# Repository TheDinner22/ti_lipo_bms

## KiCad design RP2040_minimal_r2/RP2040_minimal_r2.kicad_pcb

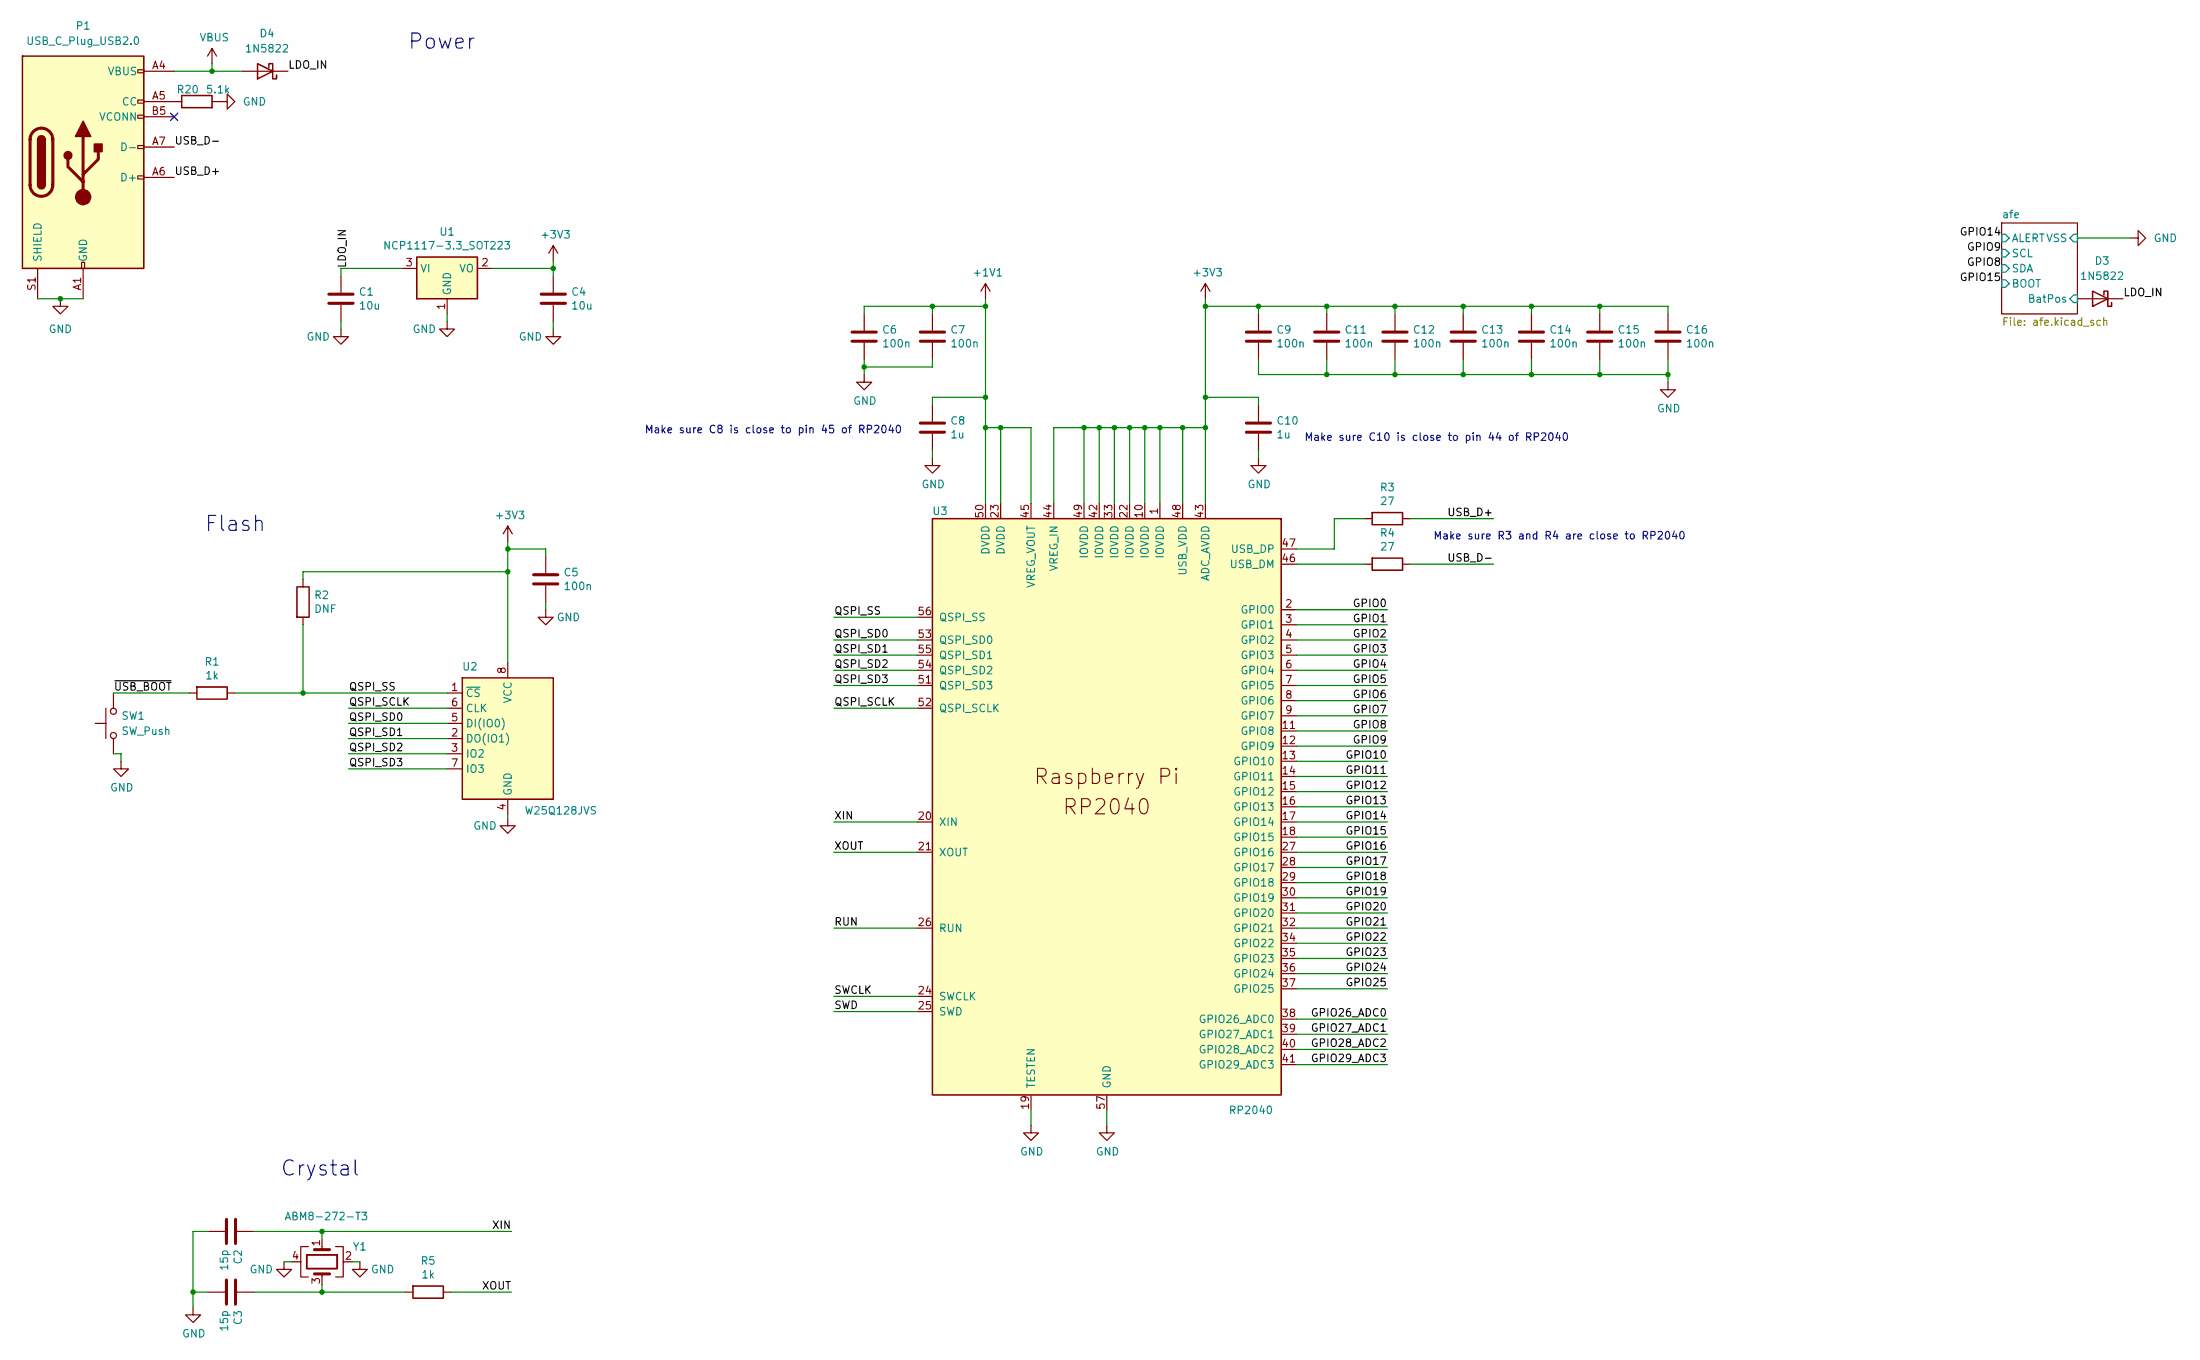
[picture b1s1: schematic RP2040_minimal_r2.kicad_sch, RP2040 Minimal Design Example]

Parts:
C1, C4: 10u; C_0805_2012Metric
C2, C3: 15p; C_0402_1005Metric
C5, C6, C7, C9, C11, C12, C13, C14, C15, C16: 100n; C_0402_1005Metric
C8, C10: 1u; C_0402_1005Metric
D3, D4: 1N5822; D_DO-201AD_P15.24mm_Horizontal
P1: USB_C_Plug_USB2.0; USB_C_Receptacle_GCT_USB4105-xx-A_16P_TopMnt_Horizontal
R1: 1k; R_0805_2012Metric_Pad1.20x1.40mm_HandSolder
R2: DNF; R_0402_1005Metric
R3, R4: 27; R_0402_1005Metric
R5: 1k; R_0402_1005Metric
R20: 5.1k; R_0805_2012Metric_Pad1.20x1.40mm_HandSolder
SW1: SW_Push; SW_Push_SPST_NO_Alps_SKRK
U1: NCP1117-3.3_SOT223; SOT-223-3_TabPin2
U2: W25Q128JVS; SOP-8_3.76x4.96mm_P1.27mm
U3: RP2040; RP2040-QFN-56
Y1: ABM8-272-T3; Crystal_SMD_3225-4Pin_3.2x2.5mm

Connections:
+1V1: C6.1, C7.1, C8.1, U3.23 (DVDD), U3.45 (VREG_VOUT), U3.50 (DVDD)
+3V3: C4.1, C5.1, C9.1, C10.1, C11.1, C12.1, C13.1, C14.1, C15.1, C16.1, R2.1, U1.2 (VO), U2.8 (VCC), U3.1 (IOVDD), U3.10 (IOVDD), U3.22 (IOVDD), U3.33 (IOVDD), U3.42 (IOVDD), U3.43 (ADC_AVDD), U3.44 (VREG_IN), U3.48 (USB_VDD), U3.49 (IOVDD)
/GPIO0: U3.2 (GPIO0)
/GPIO1: U3.3 (GPIO1)
/GPIO2: U3.4 (GPIO2)
/GPIO3: U3.5 (GPIO3)
/GPIO4: U3.6 (GPIO4)
/GPIO5: U3.7 (GPIO5)
/GPIO6: U3.8 (GPIO6)
/GPIO7: U3.9 (GPIO7)
/GPIO8: U3.11 (GPIO8); also elsewhere on the board
/GPIO9: U3.12 (GPIO9); also elsewhere on the board
/GPIO10: U3.13 (GPIO10)
/GPIO11: U3.14 (GPIO11)
/GPIO12: U3.15 (GPIO12)
/GPIO13: U3.16 (GPIO13)
/GPIO14: U3.17 (GPIO14); also elsewhere on the board
/GPIO15: U3.18 (GPIO15); also elsewhere on the board
/GPIO16: U3.27 (GPIO16)
/GPIO17: U3.28 (GPIO17)
/GPIO18: U3.29 (GPIO18)
/GPIO19: U3.30 (GPIO19)
/GPIO20: U3.31 (GPIO20)
/GPIO21: U3.32 (GPIO21)
/GPIO22: U3.34 (GPIO22)
/GPIO23: U3.35 (GPIO23)
/GPIO24: U3.36 (GPIO24)
/GPIO25: U3.37 (GPIO25)
/GPIO26_ADC0: U3.38 (GPIO26_ADC0)
/GPIO27_ADC1: U3.39 (GPIO27_ADC1)
/GPIO28_ADC2: U3.40 (GPIO28_ADC2)
/GPIO29_ADC3: U3.41 (GPIO29_ADC3)
/LDO_IN: C1.1, D3.1 (K), D4.1 (K), U1.3 (VI)
/QSPI_SCLK: U2.6 (CLK), U3.52 (QSPI_SCLK)
/QSPI_SD0: U2.5 (DI(IO0)), U3.53 (QSPI_SD0)
/QSPI_SD1: U2.2 (DO(IO1)), U3.55 (QSPI_SD1)
/QSPI_SD2: U2.3 (IO2), U3.54 (QSPI_SD2)
/QSPI_SD3: U2.7 (IO3), U3.51 (QSPI_SD3)
/QSPI_SS: R1.1, R2.2, U2.1 (~CS), U3.56 (QSPI_SS)
/RUN: U3.26 (RUN)
/SWCLK: U3.24 (SWCLK)
/SWD: U3.25 (SWD)
/USB_D+: P1.A6 (D+), R3.1
/USB_D-: P1.A7 (D-), R4.1
/XIN: C2.1, U3.20 (XIN), Y1.1
/XOUT: R5.1, U3.21 (XOUT)
/afe/BatPos: D3.2 (A); also elsewhere on the board
/~USB_BOOT: R1.2, SW1.2
GND: C1.2, C2.2, C3.2, C4.2, C5.2, C6.2, C7.2, C8.2, C9.2, C10.2, C11.2, C12.2, C13.2, C14.2, C15.2, C16.2, P1.A1 (GND), P1.A12 (GND), P1.B1 (GND), P1.B12 (GND), P1.S1 (SHIELD), R20.2, SW1.1, U1.1 (GND), U2.4 (GND), U3.19 (TESTEN), U3.57 (GND), Y1.2, Y1.4; also elsewhere on the board
unnamed: C3.1, R5.2, Y1.3
unnamed: P1.A5 (CC), R20.1
unnamed: R4.2, U3.46 (USB_DM)
unnamed: R3.2, U3.47 (USB_DP)
VBUS: D4.2 (A), P1.A4 (VBUS), P1.A9 (VBUS), P1.B4 (VBUS), P1.B9 (VBUS)

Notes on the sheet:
Power
Crystal
Make sure C8 is close to pin 45 of RP2040
Make sure C10 is close to pin 44 of RP2040
Make sure R3 and R4 are close to RP2040
Flash

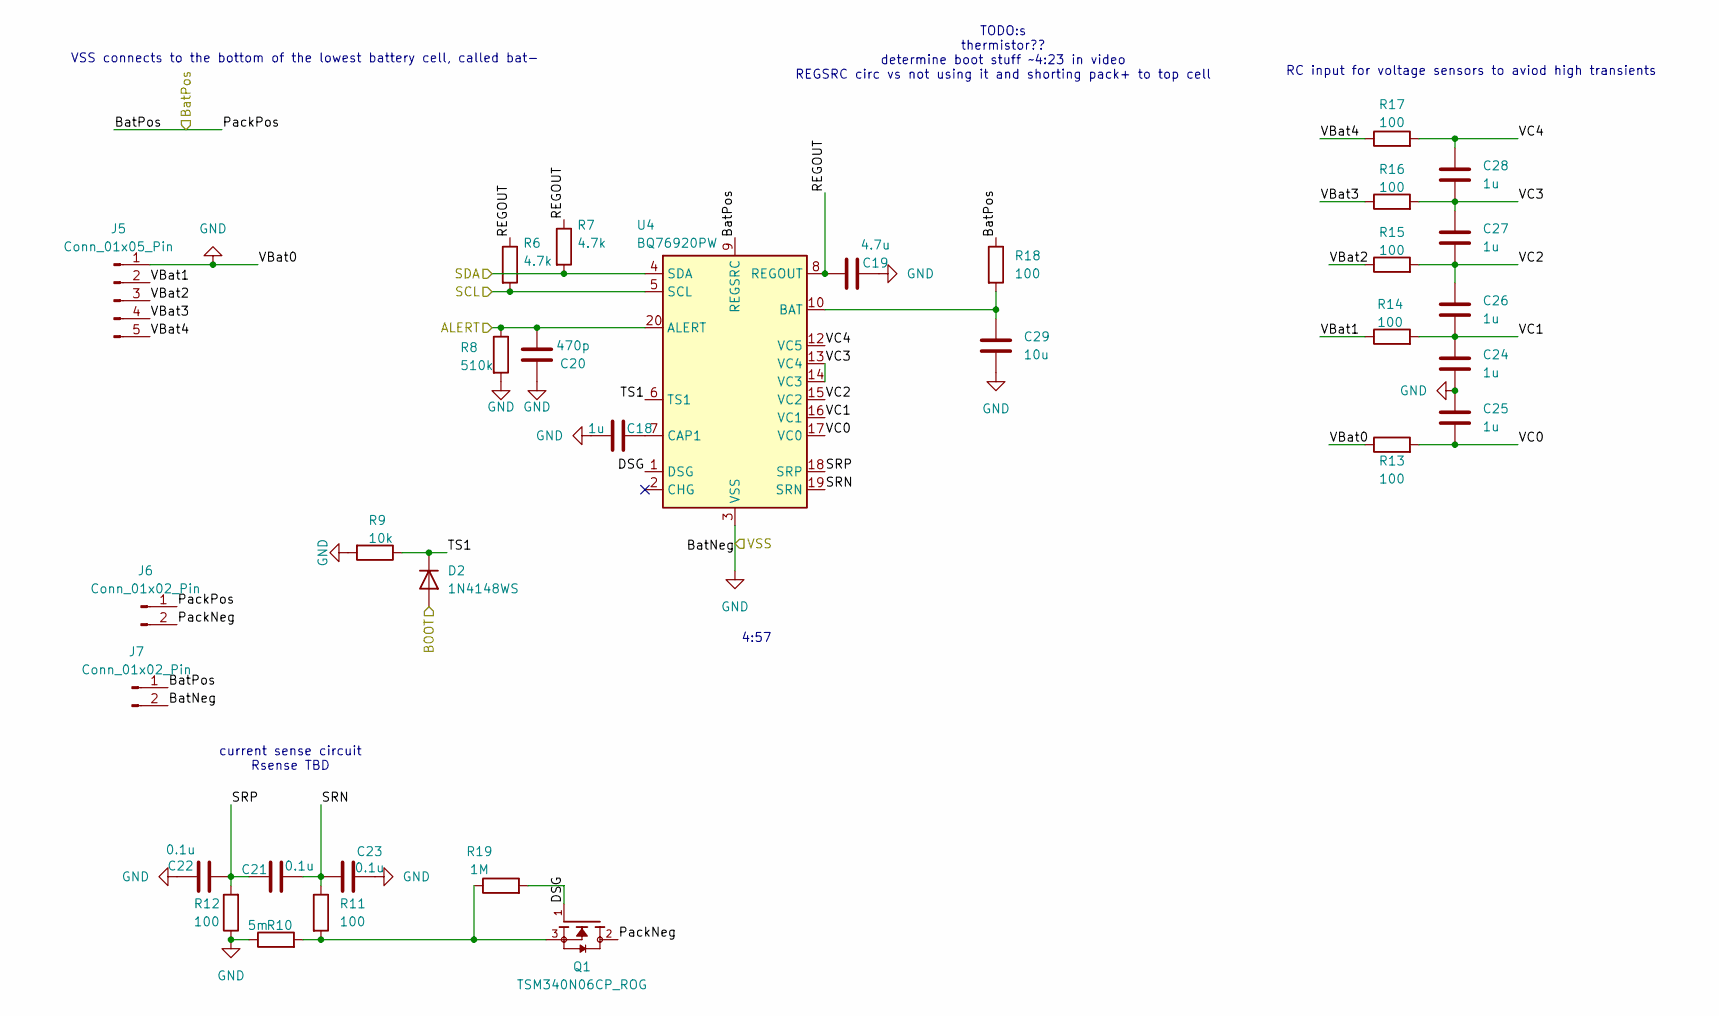
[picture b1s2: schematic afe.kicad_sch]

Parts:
C18, C24, C25, C26, C27, C28: 1u; C_0805_2012Metric
C19: 4.7u; C_0805_2012Metric
C20: 470p; C_0805_2012Metric
C21, C22, C23: 0.1u; C_0805_2012Metric
C29: 10u; C_0805_2012Metric
D2: 1N4148WS; D_SOD-323
J5: Conn_01x05_Pin; JST_EH_S5B-EH_1x05_P2.50mm_Horizontal
J6, J7: Conn_01x02_Pin; AMASS_XT30PW-F_1x02_P2.50mm_Horizontal
Q1: TSM340N06CP_ROG; TRANS_TSM340N06CP_ROG; PARTREV A1701
R6, R7: 4.7k; R_0805_2012Metric
R8: 510k; R_0805_2012Metric
R9: 10k; R_0805_2012Metric
R10: 5m; R_0805_2012Metric_Pad1.20x1.40mm_HandSolder
R11, R12, R13, R14, R15, R16, R17, R18: 100; R_0805_2012Metric_Pad1.20x1.40mm_HandSolder
R19: 1M; R_0805_2012Metric_Pad1.20x1.40mm_HandSolder
U4: BQ76920PW; TSSOP-20_4.4x6.5mm_P0.65mm

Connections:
/GPIO8: R7.2, U4.4 (SDA); also elsewhere on the board
/GPIO9: R6.2, U4.5 (SCL); also elsewhere on the board
/GPIO14: C20.2, R8.1, U4.20 (ALERT); also elsewhere on the board
/GPIO15: D2.2 (A); also elsewhere on the board
/afe/BatPos: J6.1, J7.1, R18.1, U4.9 (REGSRC); also elsewhere on the board
/afe/DSG: Q1.1, R19.2, U4.1 (DSG)
/afe/PackNeg: J6.2, Q1.2
/afe/REGOUT: C19.2, R6.1, R7.1, U4.8 (REGOUT)
/afe/SRN: C21.2, C23.2, R11.1, U4.19 (SRN)
/afe/SRP: C21.1, C22.2, R12.2, U4.18 (SRP)
/afe/TS1: D2.1 (K), R9.1, U4.6 (TS1)
/afe/VBat1: J5.2, R14.1
/afe/VBat2: J5.3, R15.1
/afe/VBat3: J5.4, R16.1
/afe/VBat4: J5.5, R17.1
/afe/VC0: C25.2, R13.2, U4.17 (VC0)
/afe/VC1: C24.1, C26.2, R14.2, U4.16 (VC1)
/afe/VC2: C26.1, C27.2, R15.2, U4.15 (VC2)
/afe/VC3: C27.1, C28.1, R16.2, U4.13 (VC4), U4.14 (VC3)
/afe/VC4: C28.2, R17.2, U4.12 (VC5)
GND: C18.1, C19.1, C20.1, C22.1, C23.1, C24.2, C25.1, C29.2, J5.1, J7.2, R8.2, R9.2, R10.1, R12.1, R13.1, U4.3 (VSS); also elsewhere on the board
unnamed: Q1.3, R10.2, R11.2, R19.1
unnamed: C29.1, R18.2, U4.10 (BAT)
unnamed: C18.2, U4.7 (CAP1)

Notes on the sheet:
4:57
RC input for voltage sensors to aviod high transients
VSS connects to the bottom of the lowest battery cell, called bat-
TODO:s thermistor?? determine boot stuff ~4:23 in video REGSRC circ vs not using it and shorting pack+ to top cell
current sense circuit Rsense TBD

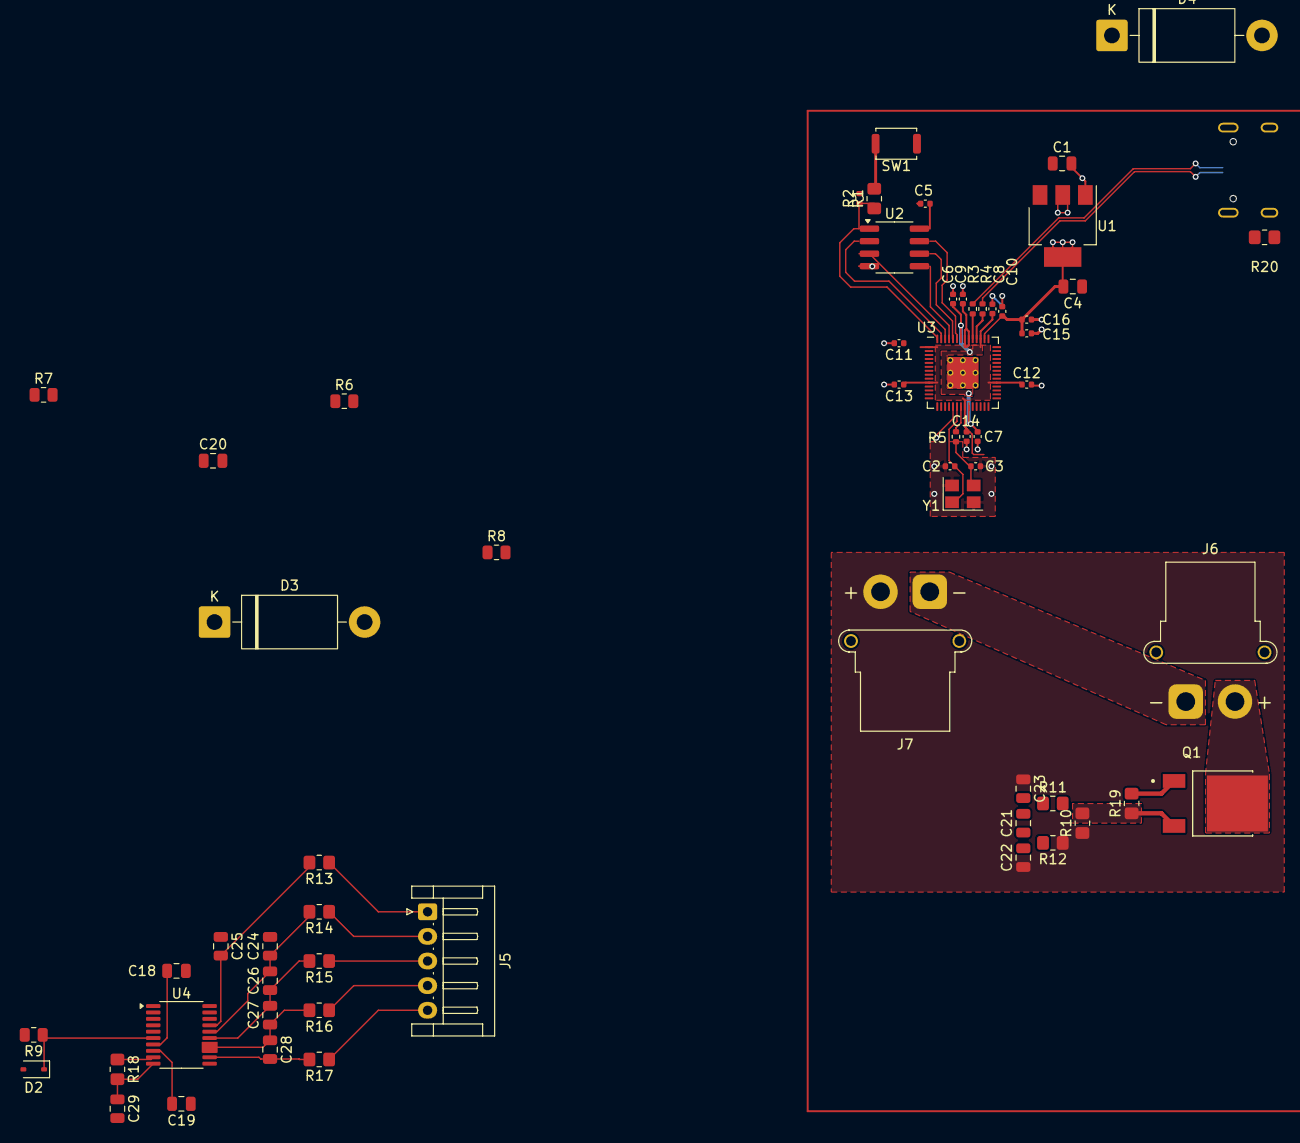
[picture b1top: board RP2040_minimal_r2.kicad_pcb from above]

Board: 2 copper layers, 62 parts (1 on the bottom side), 43 nets.

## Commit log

2025-10-06 started some pcb design ig
